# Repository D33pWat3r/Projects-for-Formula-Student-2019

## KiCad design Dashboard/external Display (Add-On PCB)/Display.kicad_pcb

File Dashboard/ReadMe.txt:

Creator: Rick Hollinski
Date: 2019-06-05

Version: 1.1

Tech Specs:
 - Spannungsversorgung: 6V - 30V
 - Leistungsverbrauch: max. 10W
 - Neopixel Strom Output: max. 2A (max. 33Leds bei 100% Weiß)
 - Mikrocontroller: Atmega328p (5V; 16MHz)
 - Programmierung: über ISP Header
 - PinOut (Arduino Labels): 4x 5V, 4x Gnd, A0-A3, 3x A4(SDA), 3x A5(SCL), 0(Rx), 1(Tx), 3, 5, 6, 7, 8, 9, 11(MoSi), 12(MiSo), 13 (SCK)

Fehler in Version 1.0:
 - Kondensator C19 darf nicht verlötet werden
 - die Ground Plane auf der Rückseite unter dem Buck Converter (MP1584), welche
	auch als Kühlkörper und als Wärmekapazität dient, war fehlerhaft eingezeichnet und ist deshalb nicht vorhanden
	
Mögliche Verbesserungen für nächste Revision (1.2):
 - 	die Pins, welche an den TM1637 angeschlossen sind, sollten gegen andere freie Pins getauscht werden.
	Somit wären die I2C Pins auch verfügbar, wenn das 7-Segment Display genutzt wird.
 
Funktionen der Platine:
  - die Platine ist Grundlegend ein Arduino Board (Atmega328p) [1]
  - für die Kommunikation mit dem CAN Bus wird der IC MCP2515 [2] genutzt und als Tranceiver MCP2551 [3]
  - die Verschaltung für CAN wurde größtenteils vom "SparkFun CAN-Bus Shield" [4] übernommen
  - für die 5V Spannungsversorgung wurde sich für einen Buck Converter [5] entschieden, da ein
	max. Strom von max. 2A benötigt wird. Ein Linear Regler würde nur heiß laufen.
  - Als Ausgabe kann ein 7-Segment Display (4 Zeichen + Punkte; gemeinsamer Plus Connector) [6] genutzt werden. Als Treiber wurde der TM1637 [7] genutzt.
  - Zudem besteht die Möglichkeit alternativ zum 7 Segment Display 2x OLED Displays (0,96 Zoll) über I2C zu benutzten.
  - Als weitere Ausgabe, kann ein LED-RGB-Stripe (basierend auf WS2812) angeschlossen werden.
  
Software Bibliotheken:
  - zur Programmierung wird das C++ Framework "Arduino Core" ab Version 1.8 empfohlen
  - bei der Auswahl des Mikrocontrollers / Entwicklerboards in der Arduino IDE kann der "Arduino UNO" ausgewählt werden
  - zur Kommunikation per CAN wird die Bibliothek von "Seeed-Studio" [8] genutzt.
  - für die Ausgabe per 7-Segment Anzeige kann die Bibliothken von "avishorp" [9] genommen werden
  - die Ausgabe per LED Stripe wird über die Adafruit Bibliothek [10] realisiert
  - für die alternative Ausgabe per OLED Displays kann die Bibliothek von "olikraus" genutzt werden [11]

  Quellverzeichnis:
[1]  Arduino-Pro-Mini_3v3.pdf
[2]  MCP2515.pdf
[3]  MCP2551.pdf
[4]  SparkFun_CAN-Bus_Shield_v13a.pdf
[5]  MP1584_r1.0.pdf
[6]  Datasheet CL5642BH.pdf
[7]  Datasheet_TM1637.pdf

[8]  https://github.com/Seeed-Studio/CAN_BUS_Shield
[9]  https://github.com/avishorp/TM1637
[10]  https://github.com/adafruit/Adafruit_NeoPixel
[11] https://github.com/olikraus/U8g2_Arduino

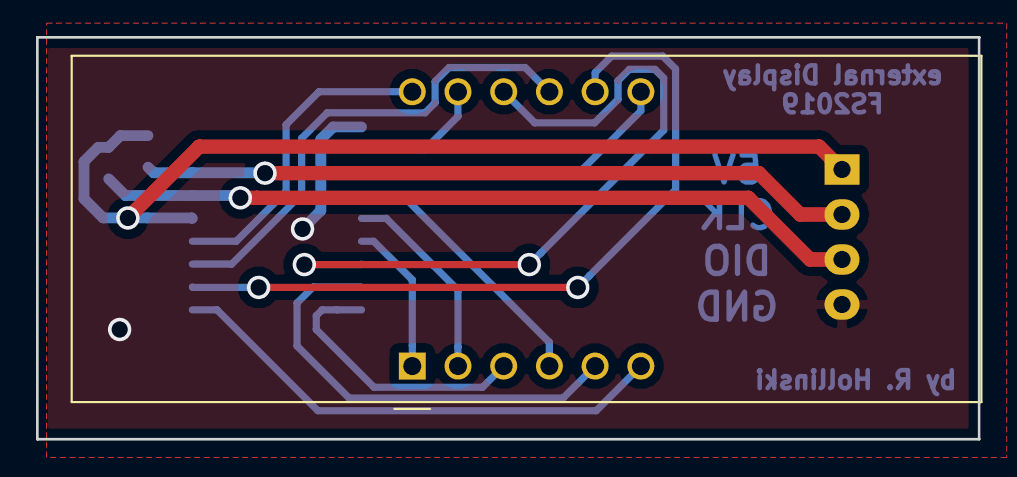
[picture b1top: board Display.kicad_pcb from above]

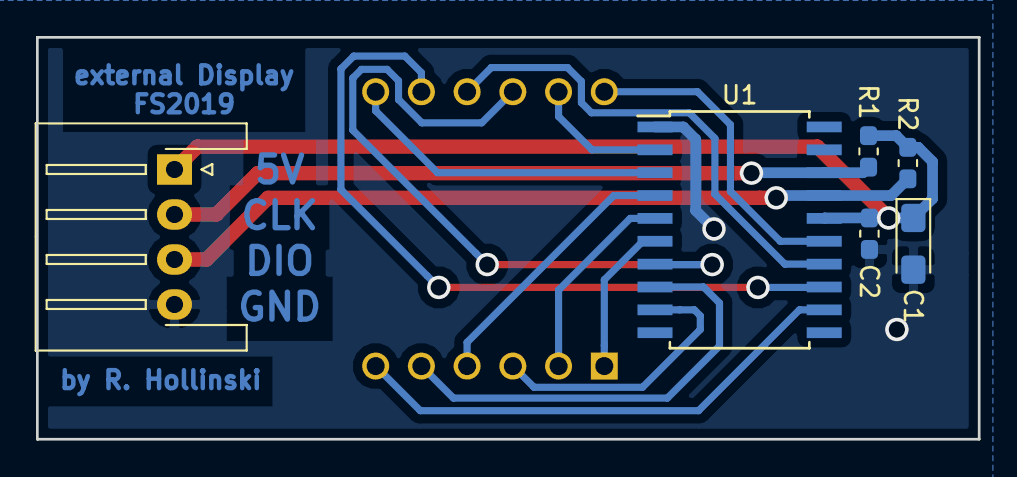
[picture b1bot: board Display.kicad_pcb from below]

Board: 2 copper layers, 52.3 x 22.3 mm, 7 parts (6 on the bottom side), 16 nets.

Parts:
C1: 100µ; CP_EIA-3216-10_Kemet-I_Pad1.58x1.35mm_HandSolder
C2: 100n; C_0603_1608Metric_Pad1.05x0.95mm_HandSolder
J1: Power; JST_XH_S04B-XH-A-1_1x04_P2.50mm_Horizontal
R1, R2: 10k; R_0603_1608Metric_Pad1.05x0.95mm_HandSolder
U1: TM1637; SOIC-20W_7.5x12.8mm_P1.27mm
U2: CA56-12EWA

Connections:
+5V: C1.1, C2.1, J1.1, R1.1, R2.1, U1.16
CLK: J1.2, R1.2, U1.18
DIO: J1.3, R2.2, U1.17
GND: C1.2, C2.2, J1.4, U1.1
Seg1: U1.15, U2.12
Seg2: U1.14, U2.9
Seg3: U1.13, U2.8
Seg4: U1.12, U2.6
a: U1.2, U2.11
b: U1.3, U2.7
c: U1.4, U2.4
d: U1.5, U2.2
dot: U1.9, U2.3
e: U1.6, U2.1
f: U1.7, U2.10
g: U1.8, U2.5

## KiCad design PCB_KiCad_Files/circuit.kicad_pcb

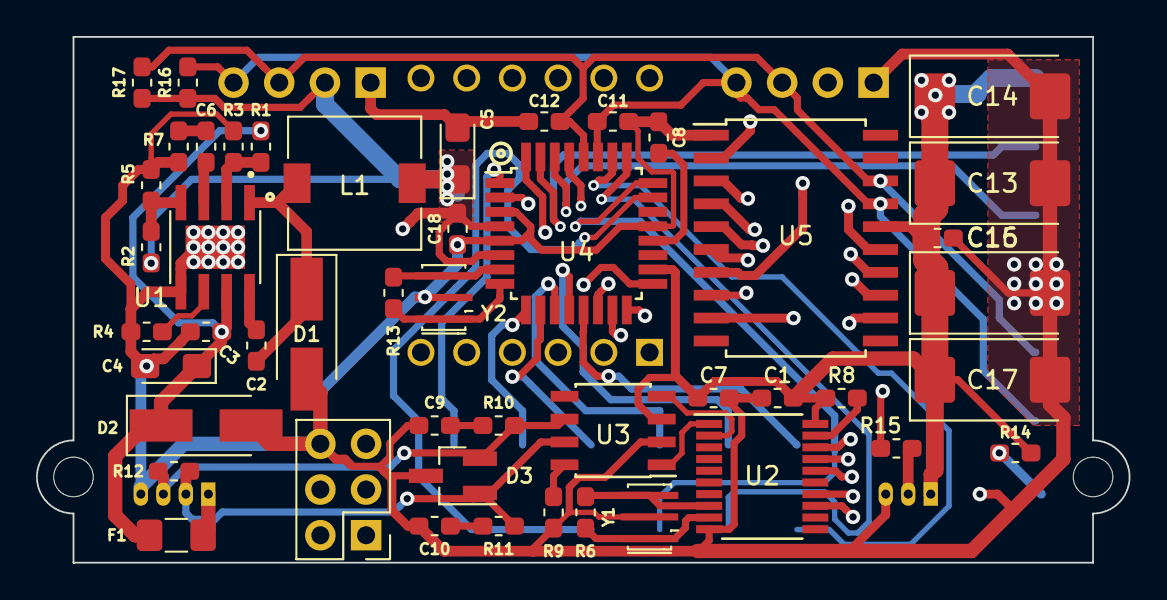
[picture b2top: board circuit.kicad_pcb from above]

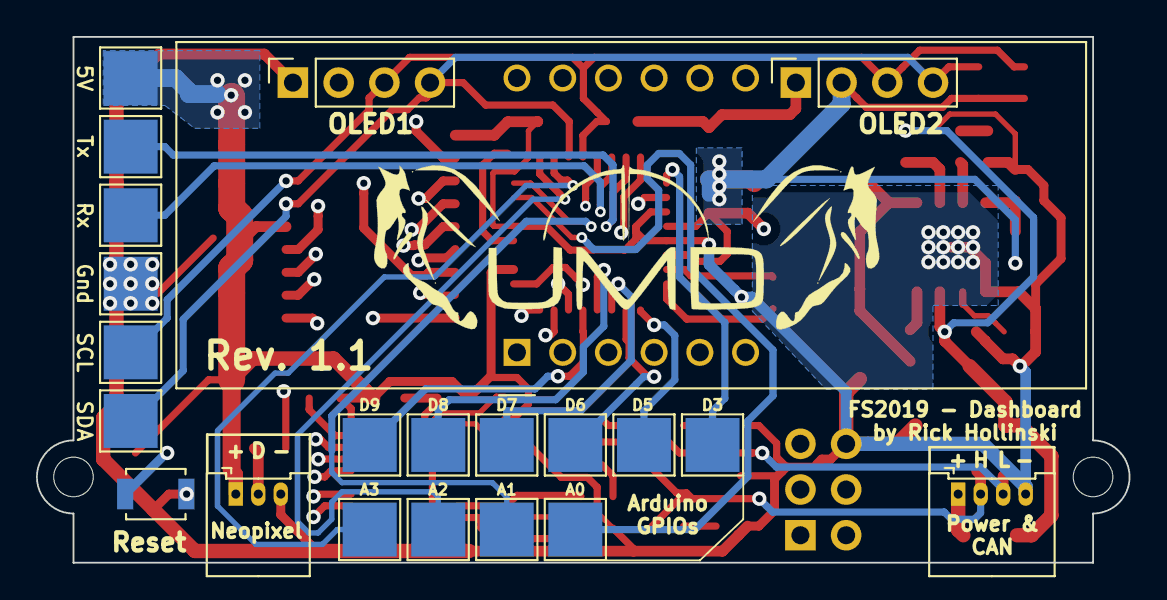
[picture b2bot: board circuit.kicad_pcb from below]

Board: 4 copper layers, 60.7 x 29.2 mm, 72 parts (22 on the bottom side), 58 nets.

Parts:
C1, C2, C3, C7, C8, C15, C18: 100n; C_0603_1608Metric_Pad1.05x0.95mm_HandSolder
C4: 10µ; CP_EIA-3216-10_Kemet-I_Pad1.58x1.35mm_HandSolder
C5: 22µ; CP_EIA-3216-10_Kemet-I_Pad1.58x1.35mm_HandSolder
C6: 150p; C_0603_1608Metric_Pad1.05x0.95mm_HandSolder
C9, C10: 560p; C_0603_1608Metric_Pad1.05x0.95mm_HandSolder
C11, C12: 100p; C_0603_1608Metric_Pad1.05x0.95mm_HandSolder
C13, C14, C16: 470µ; CP_EIA-7343-31_Kemet-D_Pad2.25x2.55mm_HandSolder
C17: 47µ; CP_EIA-7343-31_Kemet-D_Pad2.25x2.55mm_HandSolder
D1, D2: D_Schottky; D_SMA_Handsoldering
D3: PESD1CAN; SOT-23_Handsoldering
F1: Fuse; Fuse_1206_3216Metric_Pad1.42x1.75mm_HandSolder
J1: Power; Molex_PicoBlade_53048-0810_1x04_P1.25mm_Horizontal
J4: ICSP; PinHeader_2x03_P2.54mm_Vertical
J6: NeoPixel; Molex_PicoBlade_53048-0610_1x03_P1.25mm_Horizontal
J7: OLED1; PinSocket_1x04_P2.54mm_Vertical
J8: OLED2; PinSocket_1x04_P2.54mm_Vertical
L1: 4.7µ; L_7.3x7.3_H4.5
MH1, MH2: MountingHole; MountingHole_2.2mm_M2
R1, R3, R4, R7: 100k; R_0603_1608Metric_Pad1.05x0.95mm_HandSolder
R2: 43k; R_0603_1608Metric_Pad1.05x0.95mm_HandSolder
R5: 8.2k; R_0603_1608Metric_Pad1.05x0.95mm_HandSolder
R6, R13: 1M; R_0603_1608Metric_Pad1.05x0.95mm_HandSolder
R8, R9: 4,7k; R_0603_1608Metric_Pad1.05x0.95mm_HandSolder
R10, R11: 100; R_0603_1608Metric_Pad1.05x0.95mm_HandSolder
R12: 120; R_0603_1608Metric_Pad1.05x0.95mm_HandSolder
R14, R16, R17: 10k; R_0603_1608Metric_Pad1.05x0.95mm_HandSolder
R15: 330; R_0603_1608Metric_Pad1.05x0.95mm_HandSolder
SW1: Reset; SW_SPST_B3U-1000P
TP1: D3; TestPoint_Pad_3.0x3.0mm
TP2: D5; TestPoint_Pad_3.0x3.0mm
TP3: D6; TestPoint_Pad_3.0x3.0mm
TP4: D7; TestPoint_Pad_3.0x3.0mm
TP5: 5V; TestPoint_Pad_3.0x3.0mm
TP6: D8; TestPoint_Pad_3.0x3.0mm
TP7: Rx; TestPoint_Pad_3.0x3.0mm
TP8: D9; TestPoint_Pad_3.0x3.0mm
TP9: Tx; TestPoint_Pad_3.0x3.0mm
TP10: Gnd; TestPoint_Pad_3.0x3.0mm
TP11: A0; TestPoint_Pad_3.0x3.0mm
TP12: A1; TestPoint_Pad_3.0x3.0mm
TP13: A2; TestPoint_Pad_3.0x3.0mm
TP14: A3; TestPoint_Pad_3.0x3.0mm
TP15: SDA; TestPoint_Pad_3.0x3.0mm
TP16: SCL; TestPoint_Pad_3.0x3.0mm
U1: MP1584EN-LF-Z; SOIC127P600X170-9N
U2: MCP2515-IST; TSSOP-20_4.4x6.5mm_P0.65mm
U3: MCP2551-I-SN; SOIC-8_3.9x4.9mm_P1.27mm
U4: ATmega328P; TQFP-32_7x7mm_P0.8mm
U5: TM1637; SOIC-20W_7.5x12.8mm_P1.27mm
U6: CA56-12EWA
Y1, Y2: 16MHz; Resonator_SMD_muRata_CSTxExxV-3Pin_3.0x1.1mm_HandSoldering

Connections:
+5V: C1.1, C5.1, C7.1, C13.1, C14.1, C15.1, C16.1, C17.1, C18.1, J4.2, J6.1, J7.2, J8.2, L1.1, R2.1, R8.1, R14.1, R16.1, R17.1, TP5.1, U2.20, U3.3, U4.4, U4.6, U4.18, U5.16
A0: TP11.1, U4.23
A1: TP12.1, U4.24
A2: TP13.1, U4.25
A3: TP14.1, U4.26
CANH: D3.1, J1.2, R11.2, R12.1, U3.7
CANL: D3.2, J1.3, R10.2, R12.2, U3.6
CAN_INT: U2.13, U4.32
CAN_RXD: U2.2, U3.4
CAN_TXD: U2.1, U3.1
CSN: U2.18, U4.14
D3: TP1.1, U4.1
D5: TP2.1, U4.9
D6: TP3.1, U4.10
D7: TP4.1, U4.11
D8: TP6.1, U4.12
D9: TP8.1, U4.13
GND: C1.2, C3.2, C4.2, C5.2, C7.2, C8.2, C9.2, C10.2, C11.2, C12.2, C13.2, C14.2, C15.2, C16.2, C17.2, C18.2, D1.2, D2.2, D3.3, J1.4, J4.6, J6.3, J7.1, J8.1, R3.2, R4.2, R5.2, R7.2, R9.2, SW1.2, TP10.1, U1.5, U1.9, U2.10, U3.2, U4.3, U4.5, U4.21, U5.1, Y1.2, Y2.2
MISO: J4.1, U2.17, U4.16
MOSI: J4.4, U2.16, U4.15
NeoPixel: R15.1, U4.2
unnamed: C2.1, U1.8
unnamed: C2.2, D1.1, L1.2, U1.1
unnamed: C6.1, U1.3
unnamed: C6.2, R7.1
unnamed: C8.1, U4.20
unnamed: C9.1, R10.1
unnamed: C10.1, R11.1
unnamed: R2.2, R5.1, U1.4
unnamed: F1.2, J1.1
unnamed: J6.2, R15.2
unnamed: R1.2, R3.1, U1.2
unnamed: R4.1, U1.6
unnamed: R6.1, U2.9, Y1.1
unnamed: R6.2, U2.8, Y1.3
unnamed: R8.2, U2.19
unnamed: R9.1, U3.8
unnamed: R13.1, U4.8, Y2.1
unnamed: R13.2, U4.7, Y2.3
Reset: J4.5, R14.2, SW1.1, U4.29
Rx: TP7.1, U4.30
SCL: C12.1, J7.3, J8.3, R17.2, TP16.1, U4.28, U5.18
SCLK: J4.3, U2.14, U4.17
SDA: C11.1, J7.4, J8.4, R16.2, TP15.1, U4.27, U5.17
Seg1: U5.15, U6.12
Seg2: U5.14, U6.9
Seg3: U5.13, U6.8
Seg4: U5.12, U6.6
Tx: TP9.1, U4.31
VDD: C3.1, C4.1, D2.1, F1.1, R1.1, U1.7
a: U5.2, U6.11
b: U5.3, U6.7
c: U5.4, U6.4
d: U5.5, U6.2
dot: U5.9, U6.3
e: U5.6, U6.1
f: U5.7, U6.10
g: U5.8, U6.5

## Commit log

2020-06-07 compare 2 displays
    a test at begin of this project to compare 2 displays
2020-06-07 datasheet for 7Segment display
2020-06-07 add LFS config
2020-06-07 Datasheet for 4 digit 7Segment display
    typ Common Cathode
2020-06-07 Datasheet for CAN controller
    CAN controller with SPI Interface
2020-06-07 Datasheet for CAN Transceiver
2020-06-07 Datasheet for Step-Down Converter
    simple and cheap china IC for a StepDown circuit
2020-06-07 Datasheet for LED Driver (especially for 7Segment)
    this chip can handle up to 6 digits of a 7 Segment display and has a kind of I2C Interface
2020-06-07 the Pinout for a Arduino Uno Board
    this file is from [forum.arduino.cc][https://forum.arduino.cc/index.php?topic=146315.0]
2020-06-07 Schematic file for Arduino CAN Bus shield
    this file is from "http://cdn.sparkfun.com/datasheets/Dev/Arduino/Shields/SparkFun_CAN-Bus_Shield_v13a.pdf"
2020-06-07 documentation files for Arduino CAN Bus Shield
    this files are from "https://store.arduino.cc/arduino-mkr-can-shield"
2020-06-07 gitignore for KiCad Files
2020-06-07 KiCad Project files
2020-06-07 Edge Cuts export Files
2020-06-07 Gerber Export File
2020-06-07 Schematic File in Version 1.0
2020-06-07 new Schematic Export Version 1.1
    add some text labels
2020-06-07 BOM Export V1.0
    generated with "Interactive HTML BOM plugin for KiCad"
2020-06-07 new BOM export for Version 1.1
2020-06-07 move files to Project Subfolder
2020-06-07 Dashoard v1.0 (by Matthias Gramm)
    -read CAN Messages and save it
    -if no CAN Messages arrive, values for the demonstration are generated (RPM, Gear, Temperature)
    -use the LED Band as RPM visualisation
    -flicker the LED Band to show, that the Gear can be changing
    -show on the 4digit (7-Segment) Display the current gear and the rpm value
    -flicker the Display to show, that the engine temperature is to high
2020-06-07 Dashoard_v1.1 (by Rick Hollinski)
    -split the Code to different files with different characteristics
    -some variables are packed in structures
    -the config.h File is for config values only; e.g. the hardware configuration (used IO-Pins)
    -CAN functions and configs has a seperate files (ConvertCanData.h or *.cpp) for a cleaner overview
    -all other relevant functions and values are in the Dashboard.h file and seperated in different sections (e.g. Debugging, CAN, Demo Mode, RPM Band, ...)
2020-06-07 Dashoard_v1.2 (by Rick Hollinski)
    -fill the config.h file with configurations to modify the software without change the algorithm
    -add a input mode to use a pushbutton
    -there are different screens (for endurance and acceleration) for the segment display, which can switch with the pushbutton
2020-06-07 Dashoard_v1.2b (by Rick Hollinski)
    -fill the config.h file with more configurations
    -add the function ,that the demo mode can be activate by the pushbutton; but this is to buggy
2020-06-07 Dashoard_v1.2c (by Rick Hollinski)
    -add new config value in the config.h
    -delete the buggy push button functions; demo Mode can not be activate by pushbutton now
    -there are new (better) text for the different screens
    -add a new CAN function to read out the shiftLed Signal; but this new value is not used now
    -add a new screen (States), which show successive different values
    -the new "state" screen use the Led Stripe to show the actual progress of max showed states
2020-06-07 Dashoard_v1.3 (by Rick Hollinski)
    -add much more possibilies entries in the config.h file
    -add a new RPM band function, which use for different ranges the full led stripe and show it with different colors
    -add a brightness function to show different brightness level for the led stripe
2020-06-07 Dashoard_v1.4 (by Rick Hollinski)
    -some new entries in the config.h file
    -add the possibbility to change the rpm value by a potentiometer, which use one of the analog ports
    -add the shiftlight function, which use the CAN Signal
    -there are a test modus for the shiftlight, which use the pushbutton to activate the shiftlight; but the screen change function is disabled in this modus
    -there a debugging screen, which can not be selected by the pushbutton, but it can be select as the start screen after boot
2020-06-07 Dashoard_v1.4b (by Rick Hollinski)
    -add libs to specific folder
    -there are a seperate shiftlight function, which use not the CAN signal and use the RPM value
    -the 2 different shiftlight functions can be select in the config.h file
2020-06-07 revisions history
2020-06-07 ReadMe File
2020-06-07 add DemoVideo
    this movie show the first Software Version of this Project
2020-06-07 add 3D Objects export
2020-06-07 labeled PCB Picture on the device mounted side
2020-06-07 labeled PCB Picture on the connector side
2020-06-07 different rendered pictures from KiCad
2020-06-07 mounting frame for the dashboard
2020-06-07 socket for a WS2812 Led Stripe
    this model is for 3D print
2020-06-07 KiCad gitignore
2020-06-07 KiCad Project
    this PCB is designed to manufactured with a "LPKF ProtoLaser U4"
2020-06-07 BOM export
2020-06-07 Gerber export
2020-06-07 export as 3D File
2020-06-07 export of the rendered PCB
    Front and Button side
2020-06-07 Mounting Box for PCB
2020-06-07 G-Code for "Anet A8" 3D Printer and Cura Project File
